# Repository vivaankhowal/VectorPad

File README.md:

# VectorPad
The VectorPad is my own custom branded Macropad to help with automating a few things around my house and daily keyboard tasks. I tried to fit as much potential in this Macropad as possible for the most amount of features. It has 9 MX Key switches plus some diodes for a matrix, a rotary encoder, a 0.91 in OLED screen, and the Seeeduino XIAO RP2040 as the microcontroller.

# CAD

# Firmware
Uses basic KMK Firmware and haven't figured out the features for each control yet. Probably will figure it out once I actually build this board.

# PCB

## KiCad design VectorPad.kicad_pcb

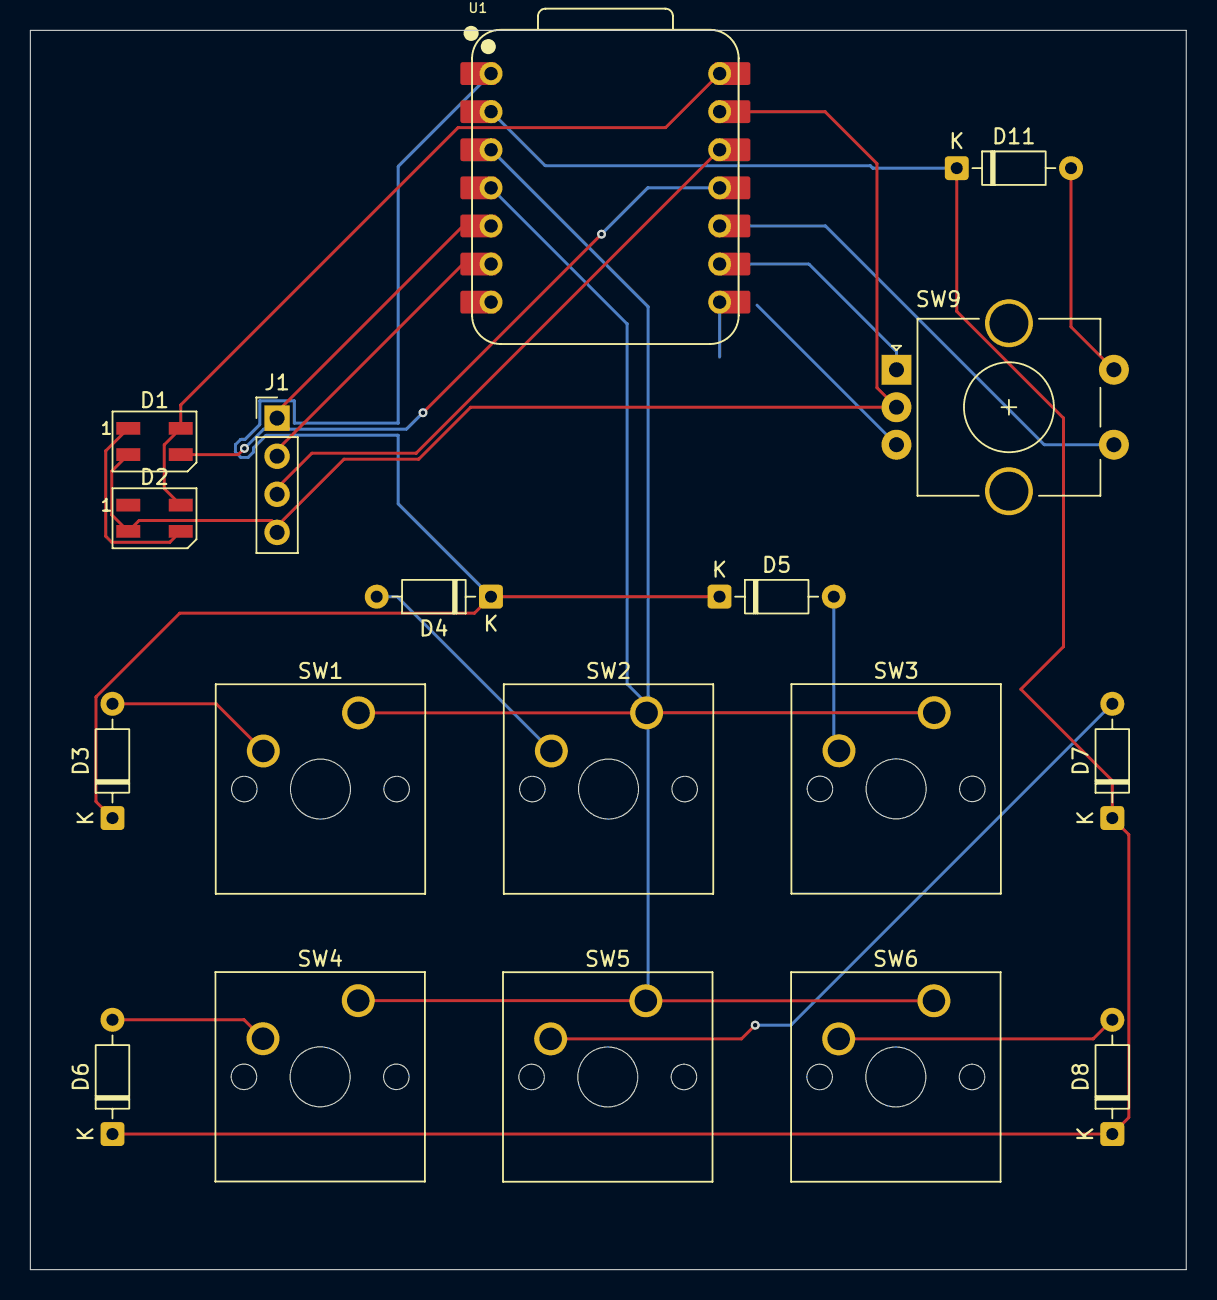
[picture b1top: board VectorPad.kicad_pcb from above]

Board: 2 copper layers, 77.1 x 82.6 mm, 18 parts (0 on the bottom side), 21 nets.

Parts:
D1, D2: LED; LED_SK6812MINI_PLCC4_3.5x3.5mm_P1.75mm
D3, D4, D5, D6, D7, D8, D11: D; D_DO-35_SOD27_P7.62mm_Horizontal
J1: OLED Display; PinHeader_1x04_P2.54mm_Vertical
SW1, SW2, SW3, SW4, SW5, SW6: Keyswitch; SW_Cherry_MX_1.00u_PCB
SW9: Knob; RotaryEncoder_Alps_EC11E-Switch_Vertical_H20mm_CircularMoun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
U1: Microcontroller; XIAO-RP2040-DIP

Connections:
GND: D1.2 (VSS), D2.2 (VSS), J1.4, SW9.C, U1.13 (GND)
unnamed: D1.3 (DIN), U1.11 (GPIO3/MOSI)
unnamed: D1.1 (DOUT), D2.3 (DIN)
unnamed: D1.4 (VDD), D2.4 (VDD), U1.14 (VBUS)
unnamed: D3.2 (A), SW1.2
unnamed: D3.1 (K), D4.1 (K), D5.1 (K), U1.1 (GPIO26/ADC0/A0)
unnamed: D4.2 (A), SW2.2
unnamed: D5.2 (A), SW3.2
unnamed: D6.2 (A), SW4.2
unnamed: D7.2 (A), SW5.2
unnamed: D8.2 (A), SW6.2
unnamed: D11.2 (A), SW9.S2
unnamed: D6.1 (K), D7.1 (K), D8.1 (K), D11.1 (K), U1.2 (GPIO27/ADC1/A1)
unnamed: J1.1, U1.5 (GPIO6/SDA)
unnamed: J1.2, U1.6 (GPIO7/SCL)
unnamed: J1.3, U1.12 (3V3)
unnamed: SW9.B, U1.8 (GPIO1/RX)
unnamed: SW9.A, U1.9 (GPIO2/SCK)
unnamed: SW9.S1, U1.10 (GPIO4/MISO)
unnamed: SW1.1, SW2.1, SW3.1, U1.3 (GPIO28/ADC2/A2)
unnamed: SW4.1, SW5.1, SW6.1, U1.4 (GPIO29/ADC3/A3)

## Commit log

2026-02-03 Rename Full CAD Assembly.step to CAD Files/Full CAD Assembly.step
2026-02-03 Rename PCB Assembly.step to CAD Files/PCB Assembly.step
2026-02-03 Rename Rotary Encoder Knob.step to CAD Files/Rotary Encoder Knob.step
2026-02-03 Rename VectorPad Base.step to CAD Files/VectorPad Base.step
2026-02-03 Rename VectorPad Lid.step to CAD Files/VectorPad Lid.step
2026-02-03 Rename VectorPad.kicad_pcb to KiCAD Files/VectorPad.kicad_pcb
2026-02-03 Rename VectorPad.kicad_prl to KiCAD Files/VectorPad.kicad_prl
2026-02-03 Rename VectorPad.kicad_pro to KiCAD Files/VectorPad.kicad_pro
2026-02-03 Rename VectorPad.kicad_sch to KiCAD Files/VectorPad.kicad_sch
2026-02-03 Rename VectorPad-backups/VectorPad-2026-02-02_213148.zip to KiCAD Files/VectorPad-backups/VectorPad-2026-02-02_213148.zip
2026-02-06 Rename KiCAD Files/Code/Main.py to Code/Main.py
